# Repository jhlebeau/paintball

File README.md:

# paintball
Elec 327 Final Project

This repository contains the code and PCB design files for our paintball game.

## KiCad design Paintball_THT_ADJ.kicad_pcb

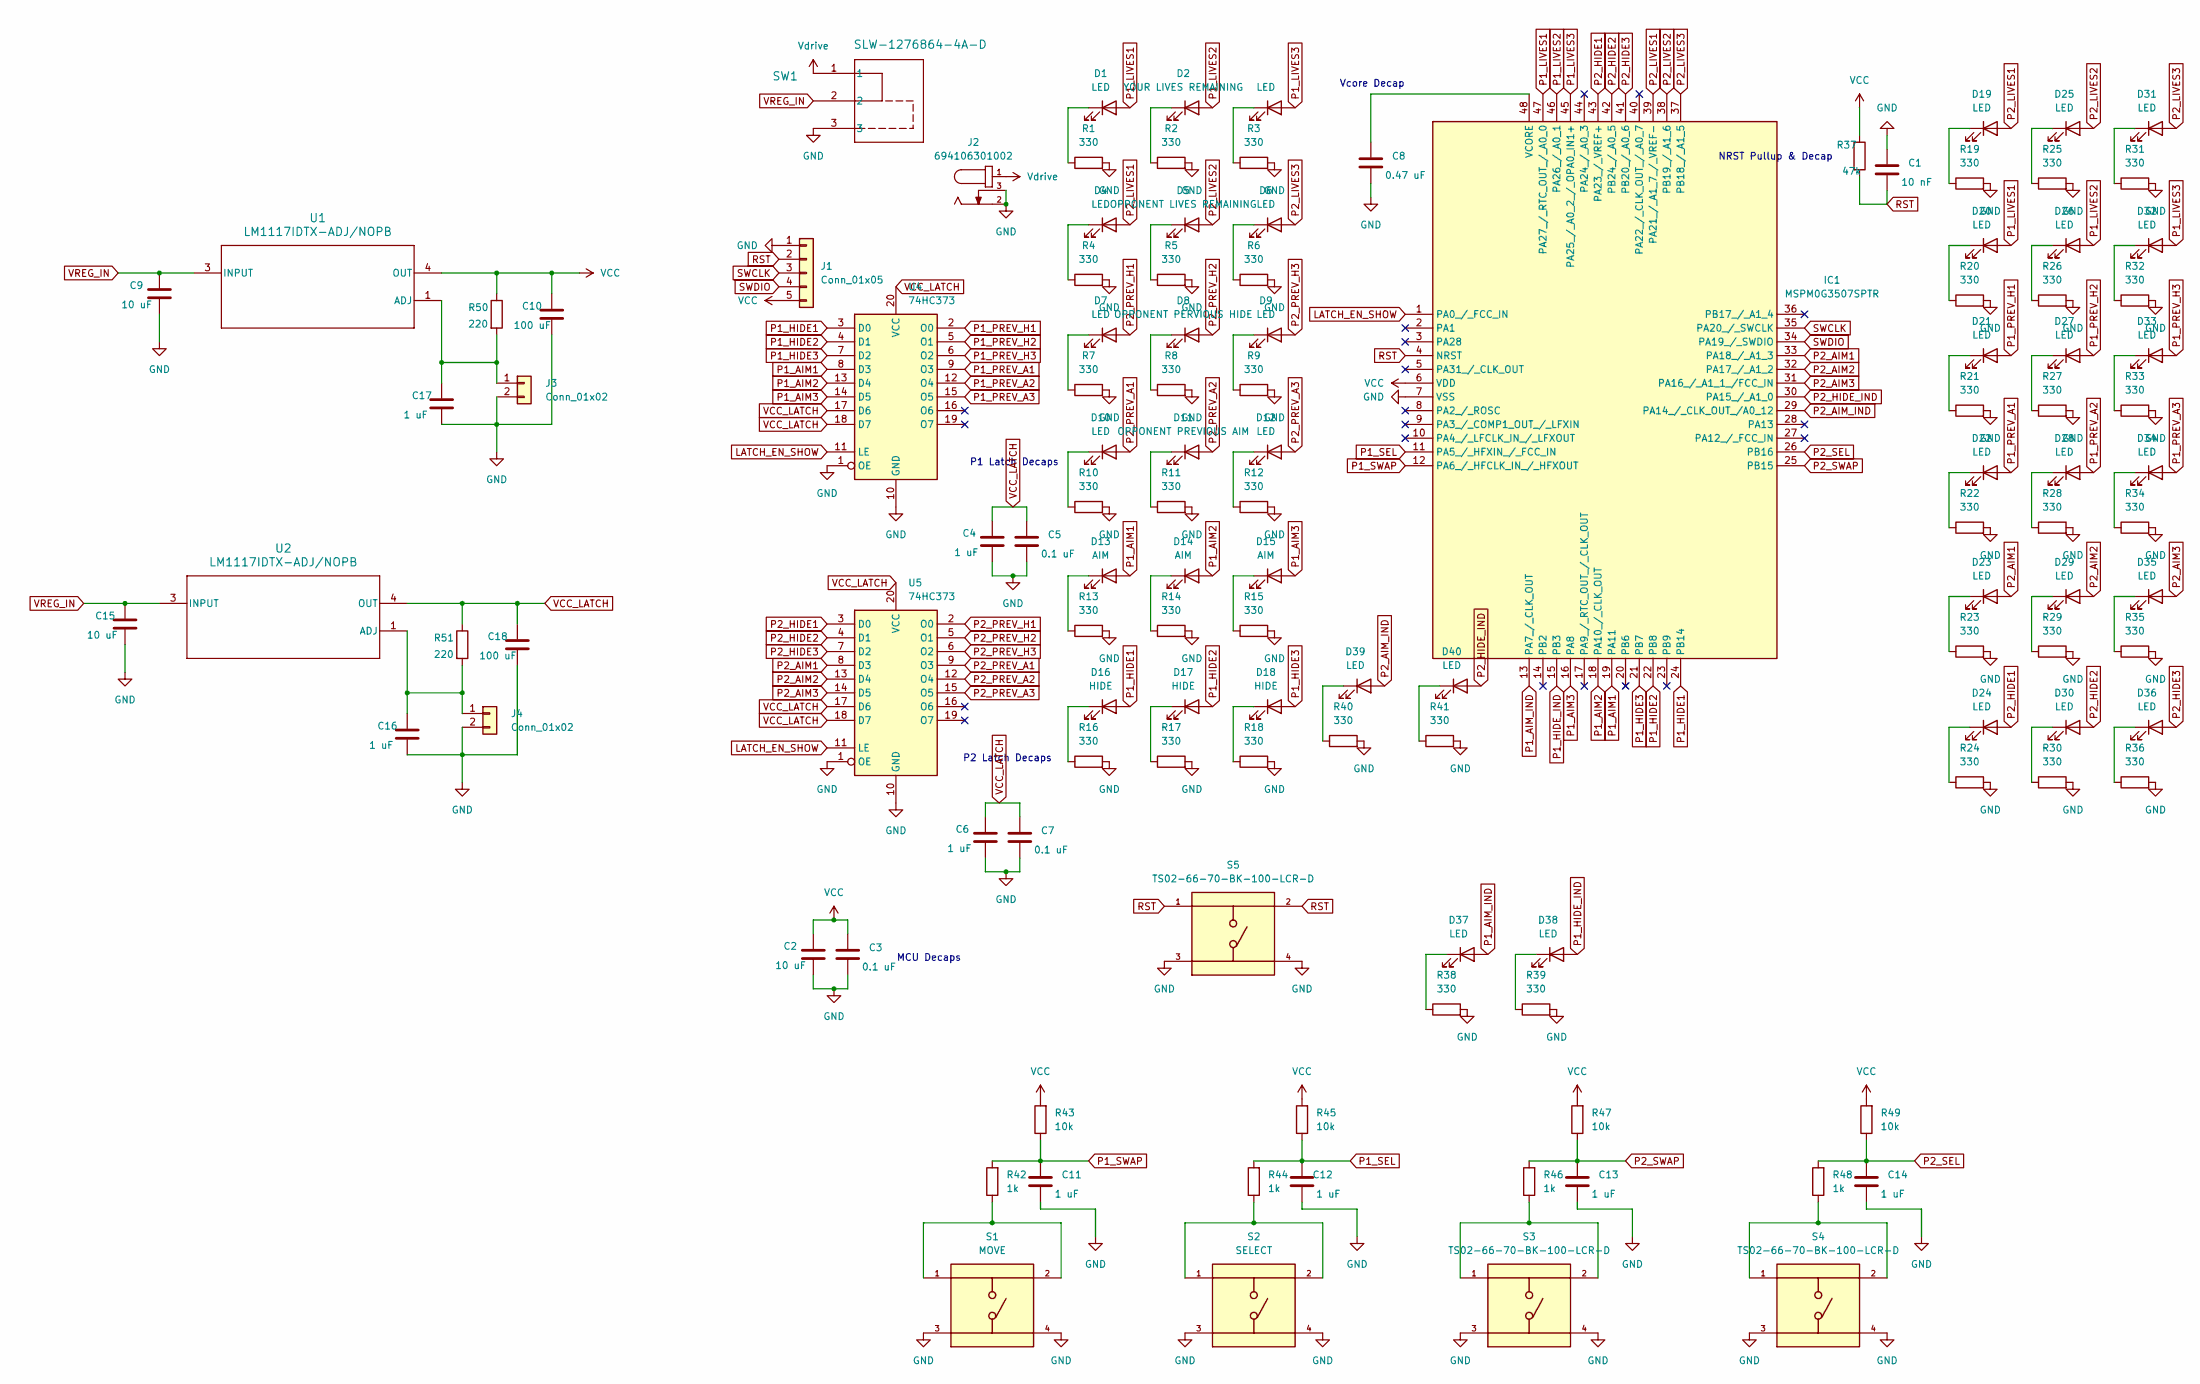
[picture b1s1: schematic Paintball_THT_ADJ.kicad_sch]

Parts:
C1: 10 nF; C_1206_3216Metric_Pad1.33x1.80mm_HandSolder; LCSC C541480
C2, C9, C15: 10 uF; C_1206_3216Metric_Pad1.33x1.80mm_HandSolder; LCSC C9807
C3, C5, C7: 0.1 uF; C_1206_3216Metric_Pad1.33x1.80mm_HandSolder; LCSC C527347
C4, C6, C11, C12, C13, C14, C16, C17: 1 uF; C_1206_3216Metric_Pad1.33x1.80mm_HandSolder; LCSC C28322
C8: 0.47 uF; C_1206_3216Metric_Pad1.33x1.80mm_HandSolder; LCSC C527350
C10, C18: 100 uF; C_1206_3216Metric_Pad1.33x1.80mm_HandSolder; LCSC C15008
D1, D3, D4, D6, D7, D9, D10, D12, D19, D20, D21, D22, D23, D24, D25, D26, D27, D28, D29, D30, D31, D32, D33, D34, D35, D36, D37, D38, D39, D40: LED; WL-TMRC_5MM
D2: YOUR LIVES REMAINING; WL-TMRC_5MM
D5: OPPONENT LIVES REMAINING; WL-TMRC_5MM
D8: OPPONENT PERVIOUS HIDE; WL-TMRC_5MM
D11: OPPONENT PREVIOUS AIM; WL-TMRC_5MM
D13, D14, D15: AIM; WL-TMRC_5MM
D16, D17, D18: HIDE; WL-TMRC_5MM
IC1: MSPM0G3507SPTR; QFP50P900X900X160-48N; Mouser Part Number 595-MSPM0G3507SPTR
J1: Conn_01x05; PinHeader_1x05_P2.54mm_Vertical; LCSC C124379
J2: 694106301002; PART-NUMBER 694106301002; LCSC C5441017
J3, J4: Conn_01x02; PinSocket_1x02_P2.54mm_Vertical
R1, R2, R3, R4, R5, R6, R7, R8, R9, R10, R11, R12, R13, R14, R15, R16, R17, R18, R19, R20, R21, R22, R23, R24, R25, R26, R27, R28, R29, R30, R31, R32, R33, R34, R35, R36, R38, R39, R40, R41: 330; R_1206_3216Metric_Pad1.30x1.75mm_HandSolder; LCSC C17930
R37: 47k; R_0402_1005Metric_Pad0.72x0.64mm_HandSolder; LCSC C25792
R42, R44, R46, R48: 1k; R_1206_3216Metric_Pad1.30x1.75mm_HandSolder; LCSC C4410
R43, R45, R47, R49: 10k; R_1210_3225Metric_Pad1.30x2.65mm_HandSolder; LCSC C104960
R50, R51: 220; R_0805_2012Metric_Pad1.20x1.40mm_HandSolder; LCSC C17557
S1: MOVE; SW_TS02-66-70-BK-100-LCR-D; PARTREV 1.0
S2: SELECT; SW_TS02-66-70-BK-100-LCR-D; PARTREV 1.0
S3, S4, S5: TS02-66-70-BK-100-LCR-D; SW_TS02-66-70-BK-100-LCR-D; PARTREV 1.0
SW1: SLW-1276864-4A-D; SLW-1276864_CUD
U1, U2: LM1117IDTX-ADJ/NOPB; NDP0003B; LCSC C2866692
U4, U5: 74HC373; DIP-20_W7.62mm; LCSC C2885

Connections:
GND: C1.1, C2.2, C3.2, C4.2, C5.2, C6.2, C7.2, C8.2, C9.2, C10.2, C11.2, C12.2, C13.2, C14.2, C15.2, C16.2, C17.2, C18.2, IC1.7 (VSS), J1.1, J2.2, J2.3, J3.2, J4.2, R1.2, R2.2, R3.2, R4.2, R5.2, R6.2, R7.2, R8.2, R9.2, R10.2, R11.2, R12.2, R13.2, R14.2, R15.2, R16.2, R17.2, R18.2, R19.2, R20.2, R21.2, R22.2, R23.2, R24.2, R25.2, R26.2, R27.2, R28.2, R29.2, R30.2, R31.2, R32.2, R33.2, R34.2, R35.2, R36.2, R38.2, R39.2, R40.2, R41.2, S1.3, S1.4, S2.3, S2.4, S3.3, S3.4, S4.3, S4.4, S5.3, S5.4, SW1.3, U4.1 (OE), U4.10 (GND), U5.1 (OE), U5.10 (GND)
LATCH_EN_SHOW: IC1.1 (PA0_/_FCC_IN), U4.11 (LE), U5.11 (LE)
unnamed: D1.1 (K), R1.1
unnamed: D2.1 (K), R2.1
unnamed: D3.1 (K), R3.1
unnamed: D4.1 (K), R4.1
unnamed: D5.1 (K), R5.1
unnamed: D6.1 (K), R6.1
unnamed: D7.1 (K), R7.1
unnamed: D8.1 (K), R8.1
unnamed: D9.1 (K), R9.1
unnamed: D10.1 (K), R10.1
unnamed: D11.1 (K), R11.1
unnamed: D12.1 (K), R12.1
unnamed: D13.1 (K), R13.1
unnamed: D14.1 (K), R14.1
unnamed: D15.1 (K), R15.1
unnamed: D16.1 (K), R16.1
unnamed: D17.1 (K), R17.1
unnamed: D18.1 (K), R18.1
unnamed: D19.1 (K), R19.1
unnamed: D20.1 (K), R20.1
unnamed: D21.1 (K), R21.1
unnamed: D22.1 (K), R22.1
unnamed: D23.1 (K), R23.1
unnamed: D24.1 (K), R24.1
unnamed: D25.1 (K), R25.1
unnamed: D26.1 (K), R26.1
unnamed: D27.1 (K), R27.1
unnamed: D28.1 (K), R28.1
unnamed: D29.1 (K), R29.1
unnamed: D30.1 (K), R30.1
unnamed: D31.1 (K), R31.1
unnamed: D32.1 (K), R32.1
unnamed: D33.1 (K), R33.1
unnamed: D34.1 (K), R34.1
unnamed: D35.1 (K), R35.1
unnamed: D36.1 (K), R36.1
unnamed: D37.1 (K), R38.1
unnamed: D38.1 (K), R39.1
unnamed: D39.1 (K), R40.1
unnamed: D40.1 (K), R41.1
unnamed: C8.1, IC1.48 (VCORE)
unnamed: C17.1, J3.1, R50.2, U1.1 (ADJ)
unnamed: C16.1, J4.1, R51.2, U2.1 (ADJ)
unnamed: R42.1, S1.1, S1.2
unnamed: R44.1, S2.1, S2.2
unnamed: R46.1, S3.1, S3.2
unnamed: R48.1, S4.1, S4.2
P1_AIM1: D13.2 (A), IC1.19 (PA11), U4.8 (D3)
P1_AIM2: D14.2 (A), IC1.18 (PA10_/_CLK_OUT), U4.13 (D4)
P1_AIM3: D15.2 (A), IC1.16 (PA8), U4.14 (D5)
P1_AIM_IND: D37.2 (A), IC1.13 (PA7_/_CLK_OUT)
P1_HIDE1: D16.2 (A), IC1.24 (PB14), U4.3 (D0)
P1_HIDE2: D17.2 (A), IC1.22 (PB8), U4.4 (D1)
P1_HIDE3: D18.2 (A), IC1.21 (PB7), U4.7 (D2)
P1_HIDE_IND: D38.2 (A), IC1.15 (PB3)
P1_LIVES1: D1.2 (A), D20.2 (A), IC1.47 (PA27_/_RTC_OUT_/_A0_0)
P1_LIVES2: D2.2 (A), D26.2 (A), IC1.46 (PA26_/_A0_1)
P1_LIVES3: D3.2 (A), D32.2 (A), IC1.45 (PA25_/_A0_2_/_OPA0_IN1+)
P1_PREV_A1: D22.2 (A), U4.9 (O3)
P1_PREV_A2: D28.2 (A), U4.12 (O4)
P1_PREV_A3: D34.2 (A), U4.15 (O5)
P1_PREV_H1: D21.2 (A), U4.2 (O0)
P1_PREV_H2: D27.2 (A), U4.5 (O1)
P1_PREV_H3: D33.2 (A), U4.6 (O2)
P1_SEL: C12.1, IC1.11 (PA5_/_HFXIN_/_FCC_IN), R44.2, R45.1
P1_SWAP: C11.1, IC1.12 (PA6_/_HFCLK_IN_/_HFXOUT), R42.2, R43.1
P2_AIM1: D23.2 (A), IC1.33 (PA18_/_A1_3), U5.8 (D3)
P2_AIM2: D29.2 (A), IC1.32 (PA17_/_A1_2), U5.13 (D4)
P2_AIM3: D35.2 (A), IC1.31 (PA16_/_A1_1_/FCC_IN), U5.14 (D5)
P2_AIM_IND: D39.2 (A), IC1.29 (PA14_/_CLK_OUT_/A0_12)
P2_HIDE1: D24.2 (A), IC1.43 (PA23_/_VREF+), U5.3 (D0)
P2_HIDE2: D30.2 (A), IC1.42 (PB24_/_A0_5), U5.4 (D1)
P2_HIDE3: D36.2 (A), IC1.41 (PB20_/_A0_6), U5.7 (D2)
P2_HIDE_IND: D40.2 (A), IC1.30 (PA15_/_A1_0)
P2_LIVES1: D4.2 (A), D19.2 (A), IC1.39 (PA21_/_A1_7_/_VREF-)
P2_LIVES2: D5.2 (A), D25.2 (A), IC1.38 (PB19_/_A1_6)
P2_LIVES3: D6.2 (A), D31.2 (A), IC1.37 (PB18_/_A1_5)
P2_PREV_A1: D10.2 (A), U5.9 (O3)
P2_PREV_A2: D11.2 (A), U5.12 (O4)
P2_PREV_A3: D12.2 (A), U5.15 (O5)
P2_PREV_H1: D7.2 (A), U5.2 (O0)
P2_PREV_H2: D8.2 (A), U5.5 (O1)
P2_PREV_H3: D9.2 (A), U5.6 (O2)
P2_SEL: C14.1, IC1.26 (PB16), R48.2, R49.1
P2_SWAP: C13.1, IC1.25 (PB15), R46.2, R47.1
RST: C1.2, IC1.4 (NRST), J1.2, R37.2, S5.1, S5.2
SWCLK: IC1.35 (PA20_/_SWCLK), J1.3
SWDIO: IC1.34 (PA19_/_SWDIO), J1.4
VCC: C2.1, C3.1, C10.1, IC1.6 (VDD), J1.5, R37.1, R43.2, R45.2, R47.2, R49.2, R50.1, U1.4 (OUT)
VCC_LATCH: C4.1, C5.1, C6.1, C7.1, C18.1, R51.1, U2.4 (OUT), U4.17 (D6), U4.18 (D7), U4.20 (VCC), U5.17 (D6), U5.18 (D7), U5.20 (VCC)
VREG_IN: C9.1, C15.1, SW1.2, U1.3 (INPUT), U2.3 (INPUT)
Vdrive: J2.1, SW1.1

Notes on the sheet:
P2 Latch Decaps
NRST Pullup & Decap
P1 Latch Decaps
MCU Decaps
Vcore Decap

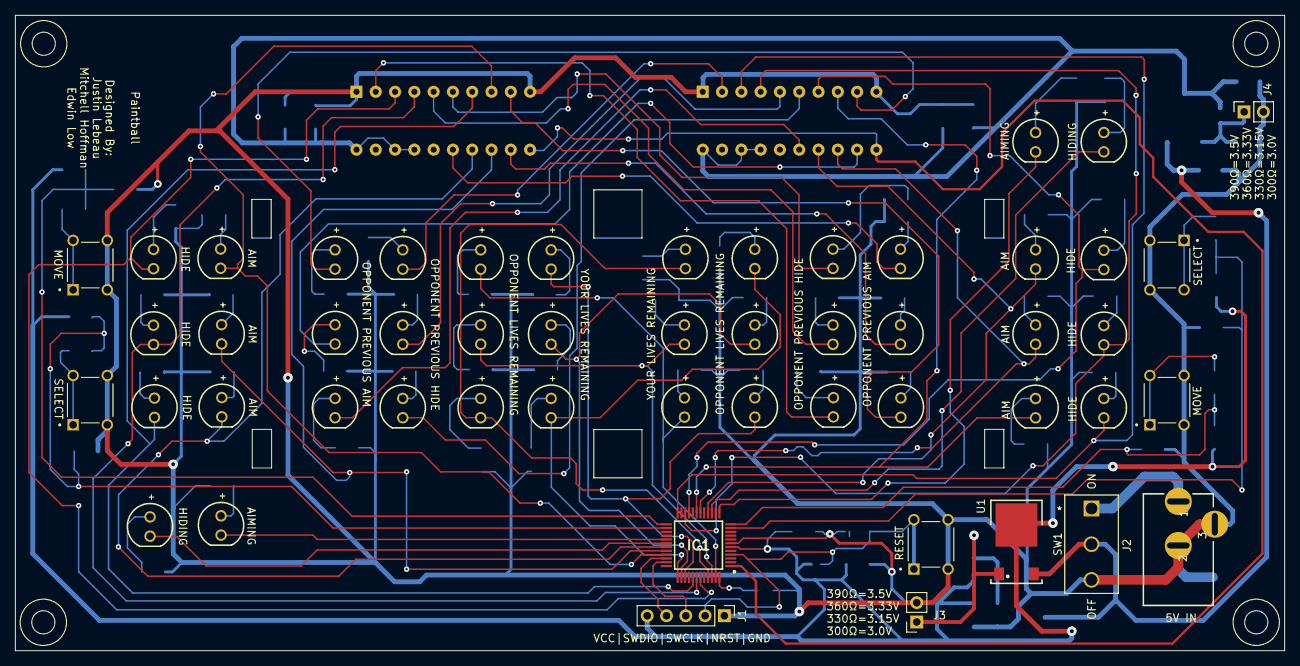
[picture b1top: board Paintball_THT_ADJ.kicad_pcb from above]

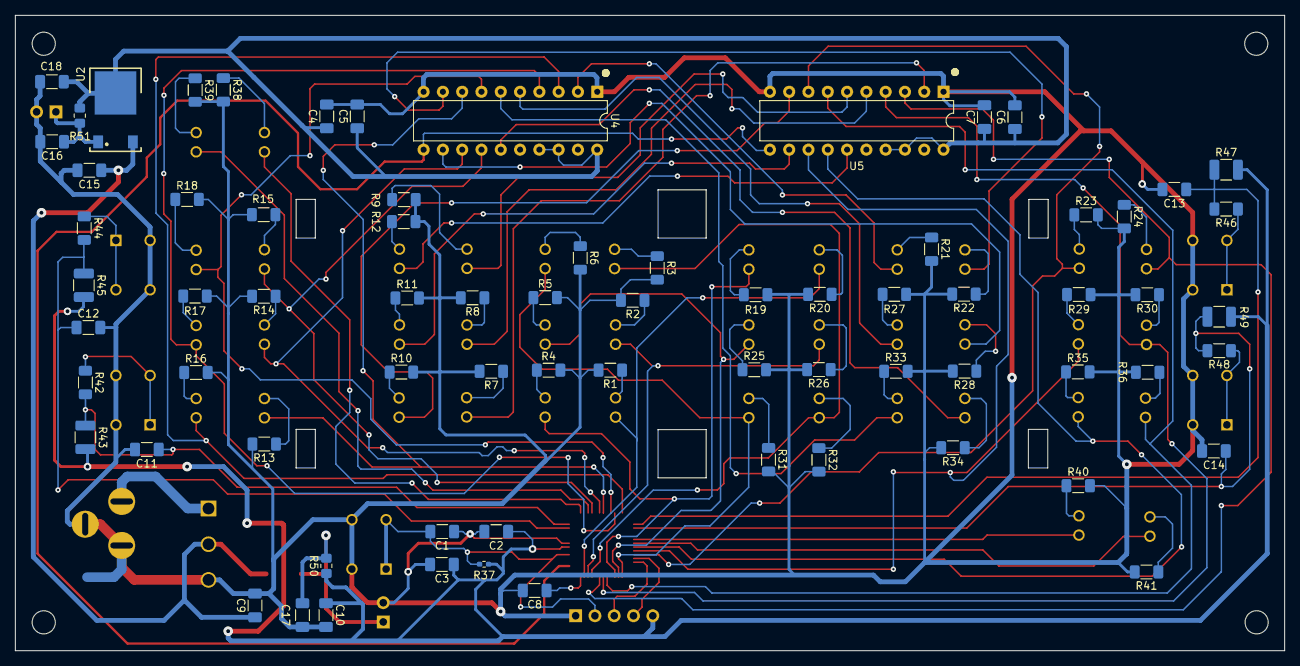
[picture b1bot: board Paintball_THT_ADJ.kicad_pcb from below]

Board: 2 copper layers, 167.1 x 83.6 mm, 124 parts (72 on the bottom side), 94 nets.

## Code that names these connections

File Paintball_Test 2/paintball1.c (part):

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// GPIOA
#define LATCH_ENABLE (0x1u)
#define P1_SELECT (0x1u << 5)
#define P1_SWAP (0x1u << 6)
#define P1_AIM_IND (0x1u << 7)
#define P1_AIM_3 (0x1u << 8)
#define P1_AIM_2 (0x1u << 10)
#define P1_AIM_1 (0x1u << 11)
#define P2_AIM_IND (0x1u << 14)
#define P2_HIDE_IND (0x1u << 15)
#define P2_AIM_3 (0x1u << 16)
#define P2_AIM_2 (0x1u << 17)
#define P2_AIM_1 (0x1u << 18)
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#define P1_LIVES_1 (0x1u << 27)

//GPIOB
#define P1_HIDE_IND (0x1u << 3)
#define P1_HIDE_3 (0x1u << 7)
#define P1_HIDE_2 (0x1u << 8)
#define P1_HIDE_1 (0x1u << 14)
#define P2_SWAP (0x1u << 15)
#define P2_SELECT (0x1u << 16)
#define P2_LIVES_3 (0x1u << 18)
#define P2_LIVES_2 (0x1u << 19)
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    IOMUX->SECCFG.PINCM[(IOMUX_PINCM33)] = (IOMUX_PINCM_PC_CONNECTED | ((uint32_t) 0x00000001 | IOMUX_PINCM_INENA_ENABLE));

    // 4. Clear pins (set values to 0)
    GPIOA->DOUTCLR31_0 =  (LATCH_ENABLE | P1_SELECT | P1_SWAP | P1_AIM_IND | P1_AIM_3 | P1_AIM_2 | P1_AIM_1 | P2_AIM_IND | P2_HIDE_IND);
    GPIOA->DOUTCLR31_0 |= (P2_AIM_3 | P2_AIM_2 | P2_AIM_1 | P2_LIVES_1 | P2_HIDE_1 | P1_LIVES_3 | P1_LIVES_2 | P1_LIVES_1);

    GPIOB->DOUTCLR31_0 = (P1_HIDE_IND | P1_HIDE_3 | P1_HIDE_2 | P1_HIDE_1 | P2_SELECT | P2_SWAP | P2_LIVES_3 | P2_LIVES_2 | P2_HIDE_3 | P2_HIDE_2);


    // 5. Enable GPIO output
    GPIOA->DOESET31_0 =  (LATCH_ENABLE | P1_AIM_IND | P1_AIM_3 | P1_AIM_2 | P1_AIM_1 | P2_AIM_IND | P2_HIDE_IND);
    GPIOA->DOESET31_0 |= (P2_AIM_3 | P2_AIM_2 | P2_AIM_1 | P2_LIVES_1 | P2_HIDE_1 | P1_LIVES_3 | P1_LIVES_2 | P1_LIVES_1);

    GPIOB->DOESET31_0 = (P1_HIDE_IND | P1_HIDE_3 | P1_HIDE_2 | P1_HIDE_1 | P2_LIVES_3 | P2_LIVES_2 | P2_HIDE_3 | P2_HIDE_2);

    // 6. Enable GPIO input on the buttons

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        switch (next_state) {
        case WAIT_FOR_INPUT:
            if ((p1_hid == 0) & (p1_aimed == 0)){
                GPIOB -> DOUTSET31_0 = P1_HIDE_IND;
                GPIOA -> DOUTCLR31_0 = P1_AIM_IND;
                if (((GPIOA->DIN31_0) & P1_SELECT) == 0){
                    p1_hid = 1;
                    p1_button_pressed = 1;
                }
                else if (((GPIOA->DIN31_0) & P1_SWAP) == 0){
                    if (p1_button_pressed == 0){
                        if (p1hide_loc == 0b100){
                            p1hide_loc = 0b010;
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                }
            }
            else if ((p1_hid == 1) & (p1_aimed ==0)){
                GPIOB -> DOUTCLR31_0 = P1_HIDE_IND;
                GPIOA -> DOUTSET31_0 = P1_AIM_IND;
                if (((GPIOA->DIN31_0) & P1_SELECT) == 0){
                    if (p1_button_pressed == 0){
                        p1_aimed = 1;
                    }
                    p1_button_pressed = 1;
                    GPIOA -> DOUTCLR31_0 = P1_AIM_IND;
                }
                else if (((GPIOA->DIN31_0) & P1_SWAP) == 0){
                    if (p1_button_pressed == 0){
                      if (p1aim_loc == 0b100){
                          p1aim_loc = 0b010;
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                }
            }
            if ((p2_hid == 0) & (p2_aimed == 0)){
                GPIOA -> DOUTSET31_0 = P2_HIDE_IND;
                GPIOA -> DOUTCLR31_0 = P2_AIM_IND;
                if (((GPIOB->DIN31_0) & P2_SELECT) == 0){
                    p2_hid = 1;
                    p2_button_pressed = 1;
                }
                else if (((GPIOB->DIN31_0) & P2_SWAP) == 0){
                    if (p2_button_pressed == 0){
                        if (p2hide_loc == 0b100){
                            p2hide_loc = 0b010;
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                }
            }
            else if ((p2_hid == 1) & (p2_aimed ==0)){
                GPIOA -> DOUTCLR31_0 = P2_HIDE_IND;
                GPIOA -> DOUTSET31_0 = P2_AIM_IND;
                if (((GPIOB->DIN31_0) & P2_SELECT) == 0){
                    if (p2_button_pressed == 0){
                        p2_aimed = 1;
                    }
                    p2_button_pressed = 1;
                    GPIOA -> DOUTCLR31_0 = P2_AIM_IND;
                }
                else if (((GPIOB->DIN31_0) & P2_SWAP) == 0){
                    if (p2_button_pressed == 0){
                      if (p2aim_loc == 0b100){
                          p2aim_loc = 0b010;
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            p2_hid = 0;
            p1_button_pressed = 0;
            p2_button_pressed = 0;
//            GPIOA -> DOUTCLR31_0 = P1_AIM_IND;
//            GPIOA -> DOUTCLR31_0 = P2_AIM_IND;
            GPIOA -> DOUTSET31_0 = LATCH_ENABLE;
            delay_cycles(LATCH_DELAY);
            GPIOA -> DOUTCLR31_0 = LATCH_ENABLE;
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}

void reset_outputs(){
    GPIOA->DOUTCLR31_0 =  (LATCH_ENABLE | P1_SELECT | P1_SWAP | P1_AIM_IND | P1_AIM_3 | P1_AIM_2 | P1_AIM_1 | P2_AIM_IND | P2_HIDE_IND);
    GPIOA->DOUTCLR31_0 |= (P2_AIM_3 | P2_AIM_2 | P2_AIM_1 | P2_LIVES_1 | P2_HIDE_1 | P1_LIVES_3 | P1_LIVES_2 | P1_LIVES_1);
    GPIOB->DOUTCLR31_0 = (P1_HIDE_IND | P1_HIDE_3 | P1_HIDE_2 | P1_HIDE_1 | P2_SELECT | P2_SWAP | P2_LIVES_3 | P2_LIVES_2 | P2_HIDE_3 | P2_HIDE_2);
    p1hide_loc = 0b100;
    p2hide_loc = 0b100;
    p1aim_loc = 0b100;
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

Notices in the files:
Paintball_Test 2/paintball1.c:
Copyright (c) 2023, Texas Instruments Incorporated
All rights reserved.
